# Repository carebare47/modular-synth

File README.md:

# modular-synth
Repository for the ((very) long term) modular synth project

## Modules

So far the only module that has been routed is the thomas-henry vca1.

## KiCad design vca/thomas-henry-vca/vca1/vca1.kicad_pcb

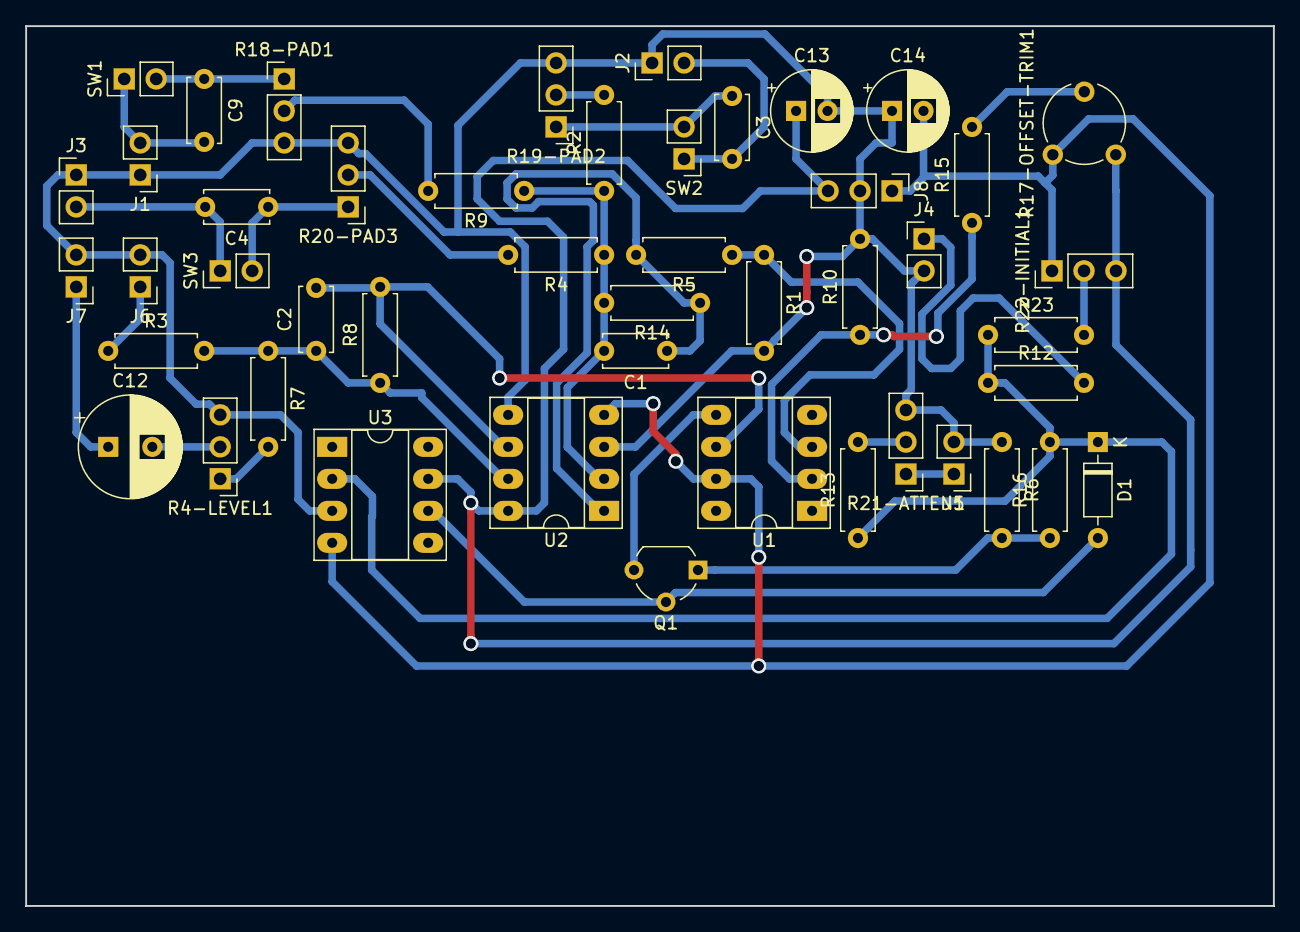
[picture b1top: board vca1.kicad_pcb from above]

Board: 2 copper layers, 99.1 x 69.9 mm, 47 parts (0 on the bottom side), 31 nets.

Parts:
C1: 10pF; C_Disc_D5.0mm_W2.5mm_P5.00mm
C2: 22pF; C_Disc_D5.0mm_W2.5mm_P5.00mm
C3, C4, C9: 0.22uF; C_Disc_D5.0mm_W2.5mm_P5.00mm
C12: 2.2uF NP; CP_Radial_D8.0mm_P3.50mm
C13, C14: 10uF; CP_Radial_D6.3mm_P2.50mm
D1: 1N914; D_DO-35_SOD27_P7.62mm_Horizontal
J1, J2, J3, J4, J5: AudioJack2; PinHeader_1x02_P2.54mm_Vertical_audio
J6: MAX OUT; PinHeader_1x02_P2.54mm_Vertical_audio
J7: LINE OUT; PinHeader_1x02_P2.54mm_Vertical_audio
J8: Conn_01x03; PinHeader_1x03_P2.54mm_Vertical
Q1: 2N3906; TO-92_Wide
R1: 22r; R_Axial_DIN0207_L6.3mm_D2.5mm_P7.62mm_Horizontal
R2, R4, R9, R12, R13, R14, R15, R16: 100k; R_Axial_DIN0207_L6.3mm_D2.5mm_P7.62mm_Horizontal
R3: 1k; R_Axial_DIN0207_L6.3mm_D2.5mm_P7.62mm_Horizontal
R4-LEVEL1: 10K; PinHeader_1x03_P2.54mm_Vertical
R5, R6: 11k; R_Axial_DIN0207_L6.3mm_D2.5mm_P7.62mm_Horizontal
R7: 15k; R_Axial_DIN0207_L6.3mm_D2.5mm_P7.62mm_Horizontal
R8: 51k; R_Axial_DIN0207_L6.3mm_D2.5mm_P7.62mm_Horizontal
R10: R; R_Axial_DIN0207_L6.3mm_D2.5mm_P7.62mm_Horizontal
R17-OFFSET-TRIM1: 100k; Potentiometer_Piher_PT-6-V_Vertical
R18-PAD1, R19-PAD2, R20-PAD3, R21-ATTEN1, R22-INITIAL1: 100K; PinHeader_1x03_P2.54mm_Vertical
R23: 330k; R_Axial_DIN0207_L6.3mm_D2.5mm_P7.62mm_Horizontal
SW1, SW2, SW3: SW_DIP_x01; PinHeader_1x02_P2.54mm_Vertical
U1: CA3080; DIP-8_W7.62mm_Socket_LongPads
U2: TL072; DIP-8_W7.62mm_Socket_LongPads
U3: TL071; DIP-8_W7.62mm_Socket_LongPads

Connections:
+15V: C13.1, J8.3, R17-OFFSET-TRIM1.1, R22-INITIAL1.3, U2.8, U3.7
-15V: C14.2, J8.1, R17-OFFSET-TRIM1.3, R22-INITIAL1.1, U1.4, U1.7, U2.4, U3.4
GNDREF: C13.2, C14.1, J1.T, J2.T, J3.T, J4.S, J5.S, J6.S, J7.S, J8.2, R1.2, R4-LEVEL1.3, R6.1, R10.2, R18-PAD1.3, R19-PAD2.3, R20-PAD3.3, R21-ATTEN1.3, U2.3, U2.5, U3.3
unnamed: C1.1, R5.2, R14.1, U2.1
unnamed: C1.2, R2.1, R4.1, R9.1, R14.2, U2.2
unnamed: C2.1, R3.2, R7.1, R8.1, U2.7
unnamed: C2.2, R8.2, U1.6, U2.6
unnamed: C3.1, R19-PAD2.1, SW2.2
unnamed: C3.2, J2.S, SW2.1
unnamed: C4.1, R20-PAD3.1, SW3.2
unnamed: C4.2, J3.S, SW3.1
unnamed: C9.1, R18-PAD1.1, SW1.2
unnamed: C9.2, J1.S, SW1.1
unnamed: C12.1, J7.T
unnamed: C12.2, R4-LEVEL1.2
unnamed: D1.1, R12.1, R13.1, R16.2, R23.1, U3.2
unnamed: D1.2, Q1.2, U3.6
unnamed: J4.T, R12.2
unnamed: J5.T, R21-ATTEN1.1
unnamed: J6.T, R3.1
unnamed: Q1.1, R6.2, R16.1
unnamed: Q1.3, U1.5
unnamed: R1.1, R5.1, U1.3
unnamed: R4-LEVEL1.1, R7.2
unnamed: R10.1, R15.1, U1.2
unnamed: R13.2, R21-ATTEN1.2
unnamed: R15.2, R17-OFFSET-TRIM1.2
unnamed: R9.2, R18-PAD1.2
unnamed: R2.2, R19-PAD2.2
unnamed: R4.2, R20-PAD3.2
unnamed: R22-INITIAL1.2, R23.2

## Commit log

2019-03-23 initial commit. VCA v1 done, not started vco
2019-03-29 new exports on vca (multiple concentric isocaltion routes
2019-04-05 testing
2019-05-05 tubescreamer cnc files
2019-05-05 @multipass@
2019-05-06 re-did 1mm paths seperately
2019-05-06 added copper removal
2019-05-06 reduced boarder to routes
2019-05-06 added output images for assembly
2019-05-06 added source gerbers
